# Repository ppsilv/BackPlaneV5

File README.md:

# BackPlaneV5
A version 5 of my backplane to serve for several CPUs.

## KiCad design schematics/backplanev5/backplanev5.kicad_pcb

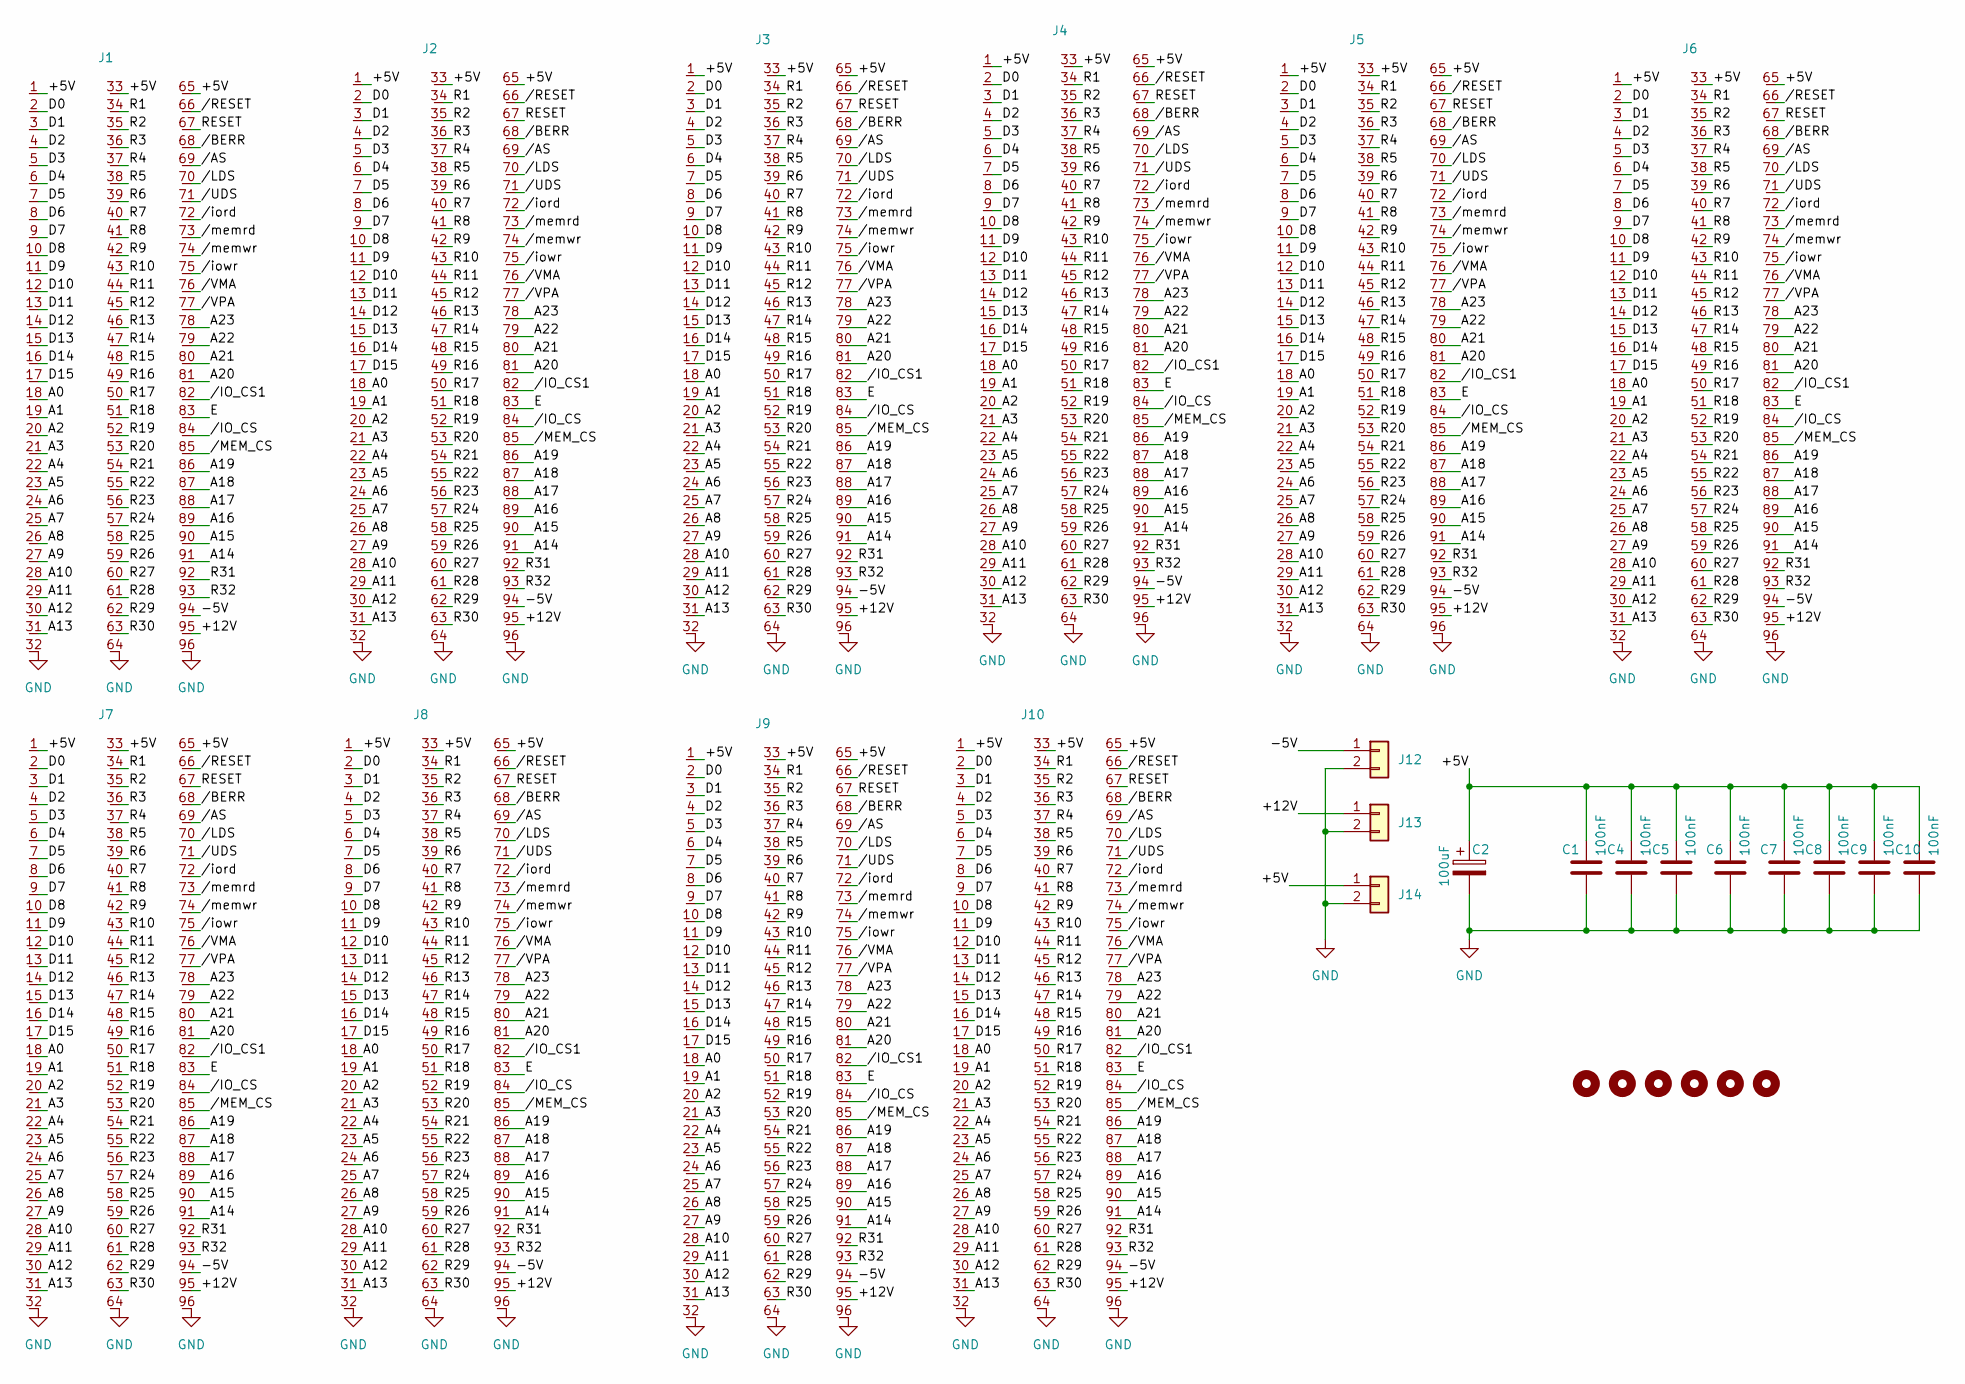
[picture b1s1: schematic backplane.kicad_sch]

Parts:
C1, C4, C5, C6, C7, C8, C9, C10: 100nF; C_Disc_D4.3mm_W1.9mm_P5.00mm
C2: 100uF; CP_Radial_D8.0mm_P5.00mm
H1, H2, H3, H4, H5, H6: MountingHole; MountingHole_3.2mm_M3
J1, J2, J3, J4, J5, J6, J7, J8, J9, J10: conn_euro96
J12, J13, J14: Conn_01x02; TerminalBlock_Phoenix_MKDS-1,5-2-5.08_1x02_P5.08mm_Horizont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

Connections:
/backplane/+5V: C1.1, C2.1, C4.1, C5.1, C6.1, C7.1, C8.1, C9.1, C10.1, J1.1, J1.33, J1.65, J2.1, J2.33, J2.65, J3.1, J3.33, J3.65, J4.1, J4.33, J4.65, J5.1, J5.33, J5.65, J6.1, J6.33, J6.65, J7.1, J7.33, J7.65, J8.1, J8.33, J8.65, J9.1, J9.33, J9.65, J10.1, J10.33, J10.65, J14.1; also elsewhere on the board
/backplane/+12V: J1.95, J2.95, J3.95, J4.95, J5.95, J6.95, J7.95, J8.95, J9.95, J10.95, J13.1
/backplane/-5V: J1.94, J2.94, J3.94, J4.94, J5.94, J6.94, J7.94, J8.94, J9.94, J10.94, J12.1
/backplane/A0: J1.18, J2.18, J3.18, J4.18, J5.18, J6.18, J7.18, J8.18, J9.18, J10.18
/backplane/A1: J1.19, J2.19, J3.19, J4.19, J5.19, J6.19, J7.19, J8.19, J9.19, J10.19
/backplane/A2: J1.20, J2.20, J3.20, J4.20, J5.20, J6.20, J7.20, J8.20, J9.20, J10.20
/backplane/A3: J1.21, J2.21, J3.21, J4.21, J5.21, J6.21, J7.21, J8.21, J9.21, J10.21
/backplane/A4: J1.22, J2.22, J3.22, J4.22, J5.22, J6.22, J7.22, J8.22, J9.22, J10.22
/backplane/A5: J1.23, J2.23, J3.23, J4.23, J5.23, J6.23, J7.23, J8.23, J9.23, J10.23
/backplane/A6: J1.24, J2.24, J3.24, J4.24, J5.24, J6.24, J7.24, J8.24, J9.24, J10.24
/backplane/A7: J1.25, J2.25, J3.25, J4.25, J5.25, J6.25, J7.25, J8.25, J9.25, J10.25
/backplane/A8: J1.26, J2.26, J3.26, J4.26, J5.26, J6.26, J7.26, J8.26, J9.26, J10.26
/backplane/A9: J1.27, J2.27, J3.27, J4.27, J5.27, J6.27, J7.27, J8.27, J9.27, J10.27
/backplane/A10: J1.28, J2.28, J3.28, J4.28, J5.28, J6.28, J7.28, J8.28, J9.28, J10.28
/backplane/A11: J1.29, J2.29, J3.29, J4.29, J5.29, J6.29, J7.29, J8.29, J9.29, J10.29
/backplane/A12: J1.30, J2.30, J3.30, J4.30, J5.30, J6.30, J7.30, J8.30, J9.30, J10.30
/backplane/A13: J1.31, J2.31, J3.31, J4.31, J5.31, J6.31, J7.31, J8.31, J9.31, J10.31
/backplane/A14: J1.91, J2.91, J3.91, J4.91, J5.91, J6.91, J7.91, J8.91, J9.91, J10.91
/backplane/A15: J1.90, J2.90, J3.90, J4.90, J5.90, J6.90, J7.90, J8.90, J9.90, J10.90
/backplane/A16: J1.89, J2.89, J3.89, J4.89, J5.89, J6.89, J7.89, J8.89, J9.89, J10.89
/backplane/A17: J1.88, J2.88, J3.88, J4.88, J5.88, J6.88, J7.88, J8.88, J9.88, J10.88
/backplane/A18: J1.87, J2.87, J3.87, J4.87, J5.87, J6.87, J7.87, J8.87, J9.87, J10.87
/backplane/A19: J1.86, J2.86, J3.86, J4.86, J5.86, J6.86, J7.86, J8.86, J9.86, J10.86
/backplane/A20: J1.81, J2.81, J3.81, J4.81, J5.81, J6.81, J7.81, J8.81, J9.81, J10.81
/backplane/A21: J1.80, J2.80, J3.80, J4.80, J5.80, J6.80, J7.80, J8.80, J9.80, J10.80
/backplane/A22: J1.79, J2.79, J3.79, J4.79, J5.79, J6.79, J7.79, J8.79, J9.79, J10.79
/backplane/A23: J1.78, J2.78, J3.78, J4.78, J5.78, J6.78, J7.78, J8.78, J9.78, J10.78
/backplane/D0: J1.2, J2.2, J3.2, J4.2, J5.2, J6.2, J7.2, J8.2, J9.2, J10.2
/backplane/D1: J1.3, J2.3, J3.3, J4.3, J5.3, J6.3, J7.3, J8.3, J9.3, J10.3
/backplane/D2: J1.4, J2.4, J3.4, J4.4, J5.4, J6.4, J7.4, J8.4, J9.4, J10.4
/backplane/D3: J1.5, J2.5, J3.5, J4.5, J5.5, J6.5, J7.5, J8.5, J9.5, J10.5
/backplane/D4: J1.6, J2.6, J3.6, J4.6, J5.6, J6.6, J7.6, J8.6, J9.6, J10.6
/backplane/D5: J1.7, J2.7, J3.7, J4.7, J5.7, J6.7, J7.7, J8.7, J9.7, J10.7
/backplane/D6: J1.8, J2.8, J3.8, J4.8, J5.8, J6.8, J7.8, J8.8, J9.8, J10.8
/backplane/D7: J1.9, J2.9, J3.9, J4.9, J5.9, J6.9, J7.9, J8.9, J9.9, J10.9
/backplane/D8: J1.10, J2.10, J3.10, J4.10, J5.10, J6.10, J7.10, J8.10, J9.10, J10.10
/backplane/D9: J1.11, J2.11, J3.11, J4.11, J5.11, J6.11, J7.11, J8.11, J9.11, J10.11
/backplane/D10: J1.12, J2.12, J3.12, J4.12, J5.12, J6.12, J7.12, J8.12, J9.12, J10.12
/backplane/D11: J1.13, J2.13, J3.13, J4.13, J5.13, J6.13, J7.13, J8.13, J9.13, J10.13
/backplane/D12: J1.14, J2.14, J3.14, J4.14, J5.14, J6.14, J7.14, J8.14, J9.14, J10.14
/backplane/D13: J1.15, J2.15, J3.15, J4.15, J5.15, J6.15, J7.15, J8.15, J9.15, J10.15
/backplane/D14: J1.16, J2.16, J3.16, J4.16, J5.16, J6.16, J7.16, J8.16, J9.16, J10.16
/backplane/D15: J1.17, J2.17, J3.17, J4.17, J5.17, J6.17, J7.17, J8.17, J9.17, J10.17
/backplane/E: J1.83, J2.83, J3.83, J4.83, J5.83, J6.83, J7.83, J8.83, J9.83, J10.83
/backplane/R1: J1.34, J2.34, J3.34, J4.34, J5.34, J6.34, J7.34, J8.34, J9.34, J10.34
/backplane/R2: J1.35, J2.35, J3.35, J4.35, J5.35, J6.35, J7.35, J8.35, J9.35, J10.35
/backplane/R3: J1.36, J2.36, J3.36, J4.36, J5.36, J6.36, J7.36, J8.36, J9.36, J10.36
/backplane/R4: J1.37, J2.37, J3.37, J4.37, J5.37, J6.37, J7.37, J8.37, J9.37, J10.37
/backplane/R5: J1.38, J2.38, J3.38, J4.38, J5.38, J6.38, J7.38, J8.38, J9.38, J10.38
/backplane/R6: J1.39, J2.39, J3.39, J4.39, J5.39, J6.39, J7.39, J8.39, J9.39, J10.39
/backplane/R7: J1.40, J2.40, J3.40, J4.40, J5.40, J6.40, J7.40, J8.40, J9.40, J10.40
/backplane/R8: J1.41, J2.41, J3.41, J4.41, J5.41, J6.41, J7.41, J8.41, J9.41, J10.41
/backplane/R9: J1.42, J2.42, J3.42, J4.42, J5.42, J6.42, J7.42, J8.42, J9.42, J10.42
/backplane/R10: J1.43, J2.43, J3.43, J4.43, J5.43, J6.43, J7.43, J8.43, J9.43, J10.43
/backplane/R11: J1.44, J2.44, J3.44, J4.44, J5.44, J6.44, J7.44, J8.44, J9.44, J10.44
/backplane/R12: J1.45, J2.45, J3.45, J4.45, J5.45, J6.45, J7.45, J8.45, J9.45, J10.45
/backplane/R13: J1.46, J2.46, J3.46, J4.46, J5.46, J6.46, J7.46, J8.46, J9.46, J10.46
/backplane/R14: J1.47, J2.47, J3.47, J4.47, J5.47, J6.47, J7.47, J8.47, J9.47, J10.47
/backplane/R15: J1.48, J2.48, J3.48, J4.48, J5.48, J6.48, J7.48, J8.48, J9.48, J10.48
/backplane/R16: J1.49, J2.49, J3.49, J4.49, J5.49, J6.49, J7.49, J8.49, J9.49, J10.49
/backplane/R17: J1.50, J2.50, J3.50, J4.50, J5.50, J6.50, J7.50, J8.50, J9.50, J10.50
/backplane/R18: J1.51, J2.51, J3.51, J4.51, J5.51, J6.51, J7.51, J8.51, J9.51, J10.51
/backplane/R19: J1.52, J2.52, J3.52, J4.52, J5.52, J6.52, J7.52, J8.52, J9.52, J10.52
/backplane/R20: J1.53, J2.53, J3.53, J4.53, J5.53, J6.53, J7.53, J8.53, J9.53, J10.53
/backplane/R21: J1.54, J2.54, J3.54, J4.54, J5.54, J6.54, J7.54, J8.54, J9.54, J10.54
/backplane/R22: J1.55, J2.55, J3.55, J4.55, J5.55, J6.55, J7.55, J8.55, J9.55, J10.55
/backplane/R23: J1.56, J2.56, J3.56, J4.56, J5.56, J6.56, J7.56, J8.56, J9.56, J10.56
/backplane/R24: J1.57, J2.57, J3.57, J4.57, J5.57, J6.57, J7.57, J8.57, J9.57, J10.57
/backplane/R25: J1.58, J2.58, J3.58, J4.58, J5.58, J6.58, J7.58, J8.58, J9.58, J10.58
/backplane/R26: J1.59, J2.59, J3.59, J4.59, J5.59, J6.59, J7.59, J8.59, J9.59, J10.59
/backplane/R27: J1.60, J2.60, J3.60, J4.60, J5.60, J6.60, J7.60, J8.60, J9.60, J10.60
/backplane/R28: J1.61, J2.61, J3.61, J4.61, J5.61, J6.61, J7.61, J8.61, J9.61, J10.61
/backplane/R29: J1.62, J2.62, J3.62, J4.62, J5.62, J6.62, J7.62, J8.62, J9.62, J10.62
/backplane/R30: J1.63, J2.63, J3.63, J4.63, J5.63, J6.63, J7.63, J8.63, J9.63, J10.63
/backplane/R31: J1.92, J2.92, J3.92, J4.92, J5.92, J6.92, J7.92, J8.92, J9.92, J10.92
/backplane/R32: J1.93, J2.93, J3.93, J4.93, J5.93, J6.93, J7.93, J8.93, J9.93, J10.93
/backplane/RESET: J1.67, J2.67, J3.67, J4.67, J5.67, J6.67, J7.67, J8.67, J9.67, J10.67
/backplane//AS: J1.69, J2.69, J3.69, J4.69, J5.69, J6.69, J7.69, J8.69, J9.69, J10.69
/backplane//BERR: J1.68, J2.68, J3.68, J4.68, J5.68, J6.68, J7.68, J8.68, J9.68, J10.68
/backplane//IO_CS: J1.84, J2.84, J3.84, J4.84, J5.84, J6.84, J7.84, J8.84, J9.84, J10.84
/backplane//IO_CS1: J1.82, J2.82, J3.82, J4.82, J5.82, J6.82, J7.82, J8.82, J9.82, J10.82
/backplane//LDS: J1.70, J2.70, J3.70, J4.70, J5.70, J6.70, J7.70, J8.70, J9.70, J10.70
/backplane//MEM_CS: J1.85, J2.85, J3.85, J4.85, J5.85, J6.85, J7.85, J8.85, J9.85, J10.85
/backplane//RESET: J1.66, J2.66, J3.66, J4.66, J5.66, J6.66, J7.66, J8.66, J9.66, J10.66
/backplane//UDS: J1.71, J2.71, J3.71, J4.71, J5.71, J6.71, J7.71, J8.71, J9.71, J10.71
/backplane//VMA: J1.76, J2.76, J3.76, J4.76, J5.76, J6.76, J7.76, J8.76, J9.76, J10.76
/backplane//VPA: J1.77, J2.77, J3.77, J4.77, J5.77, J6.77, J7.77, J8.77, J9.77, J10.77
/backplane//iord: J1.72, J2.72, J3.72, J4.72, J5.72, J6.72, J7.72, J8.72, J9.72, J10.72
/backplane//iowr: J1.75, J2.75, J3.75, J4.75, J5.75, J6.75, J7.75, J8.75, J9.75, J10.75
/backplane//memrd: J1.73, J2.73, J3.73, J4.73, J5.73, J6.73, J7.73, J8.73, J9.73, J10.73
/backplane//memwr: J1.74, J2.74, J3.74, J4.74, J5.74, J6.74, J7.74, J8.74, J9.74, J10.74
GND: C1.2, C2.2, C4.2, C5.2, C6.2, C7.2, C8.2, C9.2, C10.2, J1.32, J1.64, J1.96, J2.32, J2.64, J2.96, J3.32, J3.64, J3.96, J4.32, J4.64, J4.96, J5.32, J5.64, J5.96, J6.32, J6.64, J6.96, J7.32, J7.64, J7.96, J8.32, J8.64, J8.96, J9.32, J9.64, J9.96, J10.32, J10.64, J10.96, J12.2, J13.2, J14.2; also elsewhere on the board

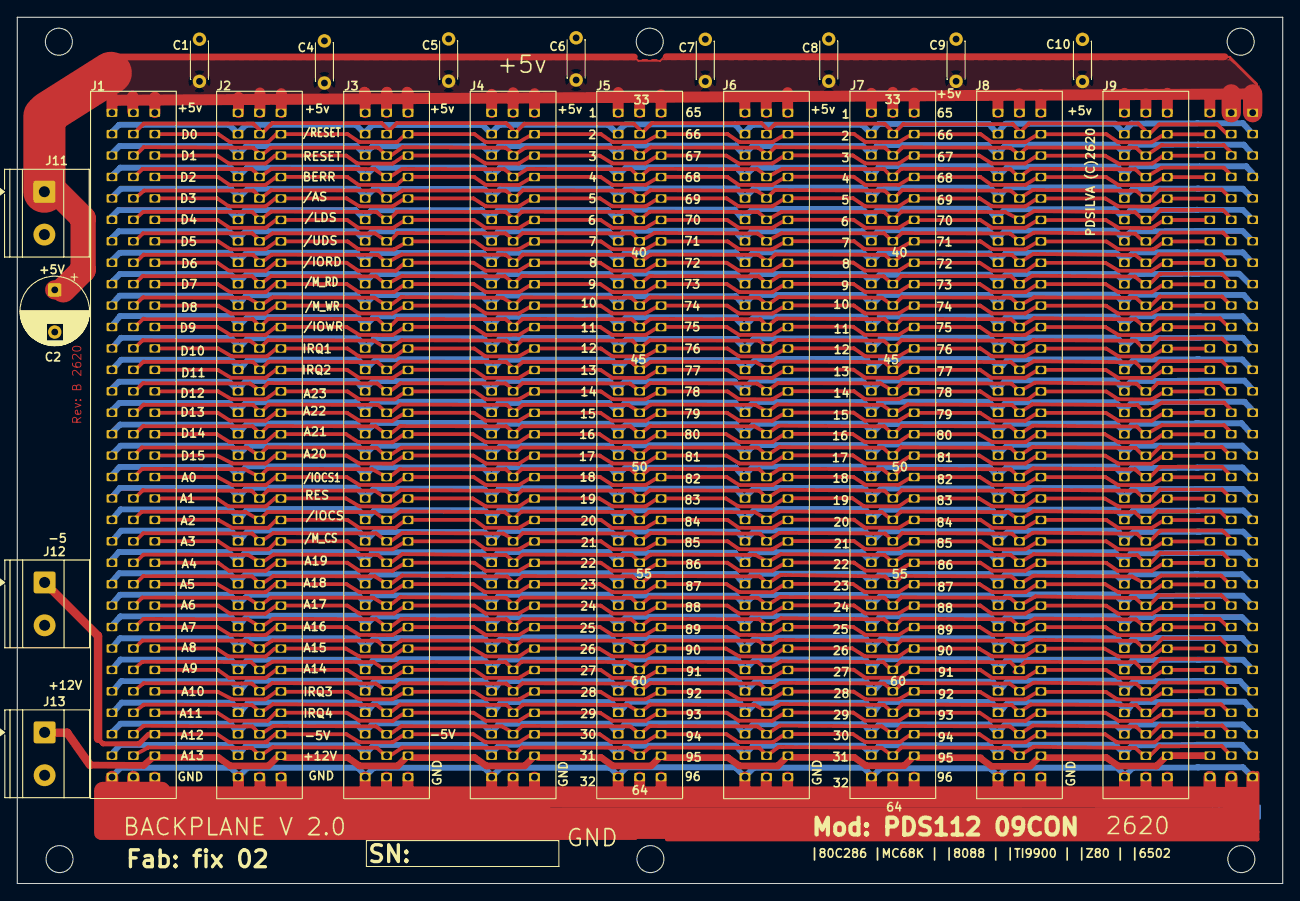
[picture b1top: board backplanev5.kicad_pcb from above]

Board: 2 copper layers, 150.0 x 102.7 mm, 28 parts (1 on the bottom side), 92 nets.

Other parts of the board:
J11: Conn_01x02; TerminalBlock_Phoenix_MKDS-1,5-2-5.08_1x02_P5.08mm_Horizont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

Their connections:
/backplane/+5V: J11.1; also elsewhere on the board
GND: J11.2; also elsewhere on the board

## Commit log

2025-11-23 Added docs...
2025-12-04 Update V1 fabrication 04-12-2025 JLCPCB
2026-01-05 added Unibus spec
2026-02-27 Manual do barramento
2026-05-13 Terminada as mudancas falta agora fazer oDRC
2026-05-14 Terminado o DRC
2026-05-14 Versao em producao
2026-05-15 CONSTRAINTS 02 UPDATING
2026-05-15 Enviado arquivo Gerber_fab_2620_02.zip para TEC-CI
